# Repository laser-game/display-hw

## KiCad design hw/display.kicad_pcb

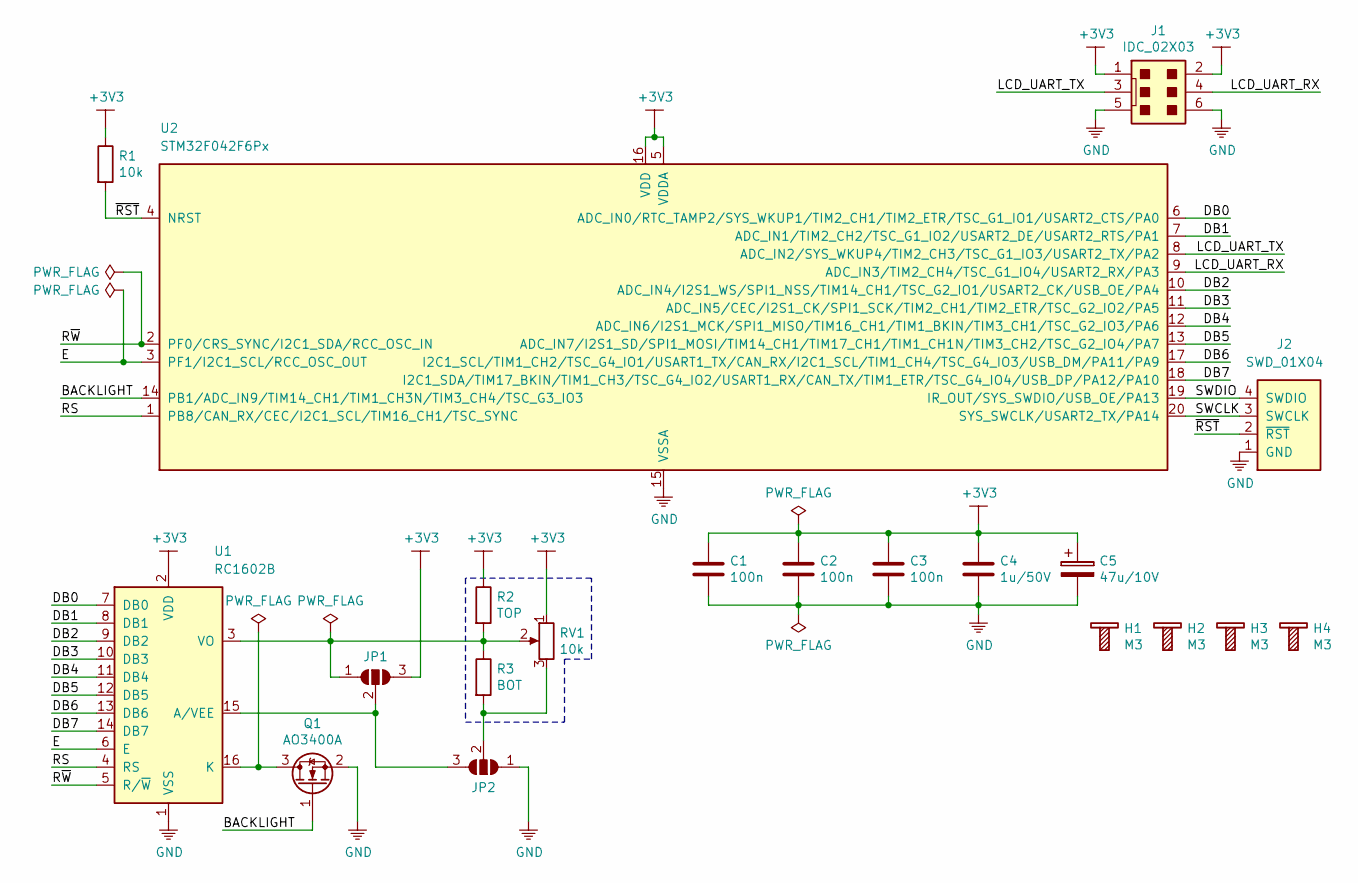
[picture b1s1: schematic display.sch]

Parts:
C1, C2, C3: 100n; C_0805_2012Metric
C4: 1u/50V; C_0805_2012Metric
C5: 47u/10V; CP_EIA-3528-21_Kemet-B
H1, H2, H3, H4: M3; Bolt_M3
J1: IDC_02X03; IDC-Header_2x03_P2.54mm_Vertical
J2: SWD_01X04; PinHeader_1x04_P2.54mm_Vertical
JP1, JP2: SolderJumper_3_Open; SolderJumper-3_P1.3mm_Open_RoundedPad1.0x1.5mm_NumberLabels
Q1: AO3400A; SOT-23
R1: 10k; R_0805_2012Metric
R2: TOP; R_0805_2012Metric
R3: BOT; R_0805_2012Metric
RV1: 10k; Potentiometer_ACP_CA9-H3,8_Horizontal
U1: RC1602B
U2: STM32F042F6Px; TSSOP-20_4.4x6.5mm_P0.65mm

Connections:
+3V3: C1.1, C2.1, C3.1, C4.1, C5.1, J1.1, J1.2, JP1.3 (B), R1.1, R2.1, RV1.1, U1.2 (VDD), U2.5 (VDDA), U2.16 (VDD)
/BACKLIGHT: Q1.1 (G), U2.14 (PB1/ADC_IN9/TIM14_CH1/TIM1_CH3N/TIM3_CH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)
/DB0: U1.7 (DB0), U2.6 (ADC_IN0/RTC_TAMP2/SYS_WKUP1/TIM2_CH1/TI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)
/DB1: U1.8 (DB1), U2.7 (ADC_IN1/TIM2_CH2/TSC_G1_IO2/USART2_DE/U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)
/DB2: U1.9 (DB2), U2.10 (ADC_IN4/I2S1_WS/SPI1_NSS/TIM14_CH1/TSC_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)
/DB3: U1.10 (DB3), U2.11 (ADC_IN5/CEC/I2S1_CK/SPI1_SCK/TIM2_CH1/T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)
/DB4: U1.11 (DB4), U2.12 (ADC_IN6/I2S1_MCK/SPI1_MISO/TIM16_CH1/TI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)
/DB5: U1.12 (DB5), U2.13 (ADC_IN7/I2S1_SD/SPI1_MOSI/TIM14_CH1/TIM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)
/DB6: U1.13 (DB6), U2.17 (I2C1_SCL/TIM1_CH2/TSC_G4_IO1/USART1_TX/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)
/DB7: U1.14 (DB7), U2.18 (I2C1_SDA/TIM17_BKIN/TIM1_CH3/TSC_G4_IO2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)
/E: U1.6 (E), U2.3 (PF1/I2C1_SCL/RCC_OSC_OUT)
/LCD_UART_RX: J1.4, U2.9 (ADC_IN3/TIM2_CH4/TSC_G1_IO4/USART2_RX/P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)
/LCD_UART_TX: J1.3, U2.8 (ADC_IN2/SYS_WKUP4/TIM2_CH3/TSC_G1_IO3/U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)
/RS: U1.4 (RS), U2.1 (PB8/CAN_RX/CEC/I2C1_SCL/TIM16_CH1/TSC_S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)
/R~W: U1.5 (R/~W), U2.2 (PF0/CRS_SYNC/I2C1_SDA/RCC_OSC_IN)
/SWCLK: J2.3 (SWCLK), U2.20 (SYS_SWCLK/USART2_TX/PA14)
/SWDIO: J2.4 (SWDIO), U2.19 (IR_OUT/SYS_SWDIO/USB_OE/PA13)
/~RST: J2.2 (~RST), R1.2, U2.4 (NRST)
GND: C1.2, C2.2, C3.2, C4.2, C5.2, J1.5, J1.6, J2.1 (GND), JP2.1 (A), Q1.2 (S), U1.1 (VSS), U2.15 (VSSA)
unnamed: JP1.1 (A), R2.2, R3.1, RV1.2, U1.3 (VO)
unnamed: JP1.2 (C), JP2.3 (B), U1.15 (A/VEE)
unnamed: JP2.2 (C), R3.2, RV1.3
unnamed: Q1.3 (D), U1.16 (K)

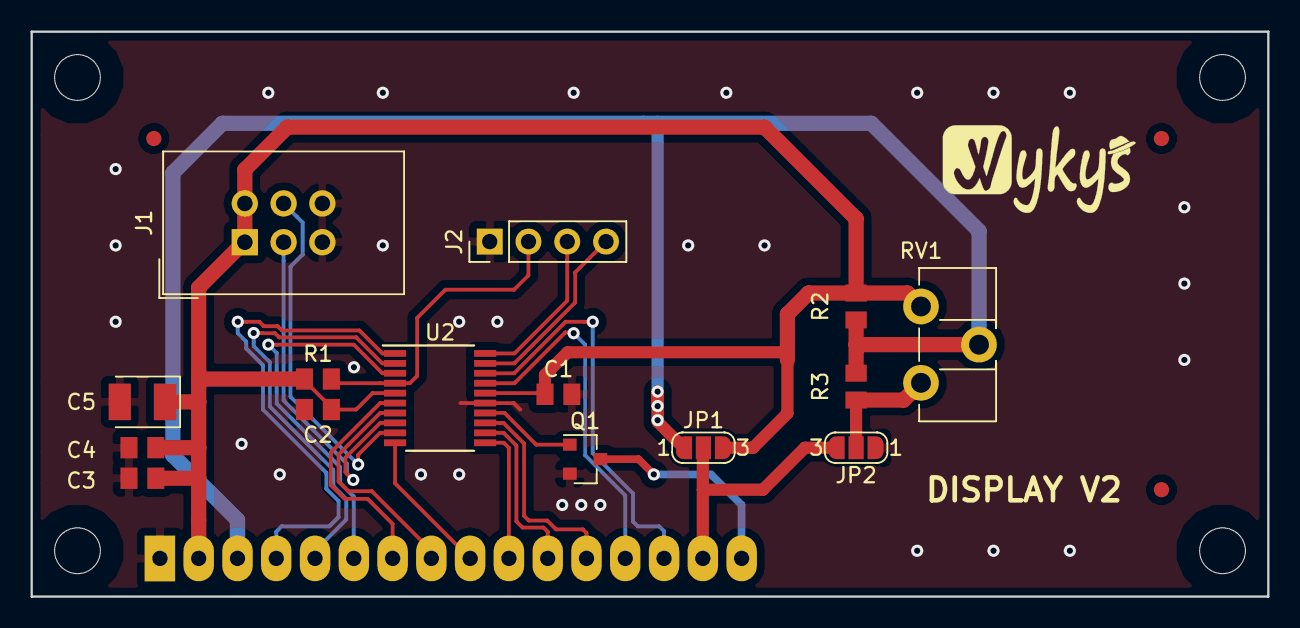
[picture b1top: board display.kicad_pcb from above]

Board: 2 copper layers, 81.0 x 37.0 mm, 20 parts (1 on the bottom side), 23 nets.

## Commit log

2018-03-30 added license and updated readme
2018-03-31 created kicad projects
2018-04-01 updated schematic
2018-04-19 updated .gitignore
2018-04-19 updated schematic universaled display and removed rst b signal
2018-04-20 placement components to pcb
2018-04-20 updated pcb
2018-04-20 added description tu schematic
2018-04-22 changed potentiometers link
2018-05-02 added boom file and schematic for fabracation
2018-05-08 updated pcb layout
2018-05-08 updated layout
2018-05-08 added gerber files
2018-05-08 added placement files
